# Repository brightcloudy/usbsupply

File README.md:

# USB Power Supply
USB-powered power supply board based around the LTC3883 Power System Manager. 

## Specifications
- 0.5-5.0 V Output Range
- 400 mA Output Current
- Programmable Current Limit
- Programmable Output Voltage

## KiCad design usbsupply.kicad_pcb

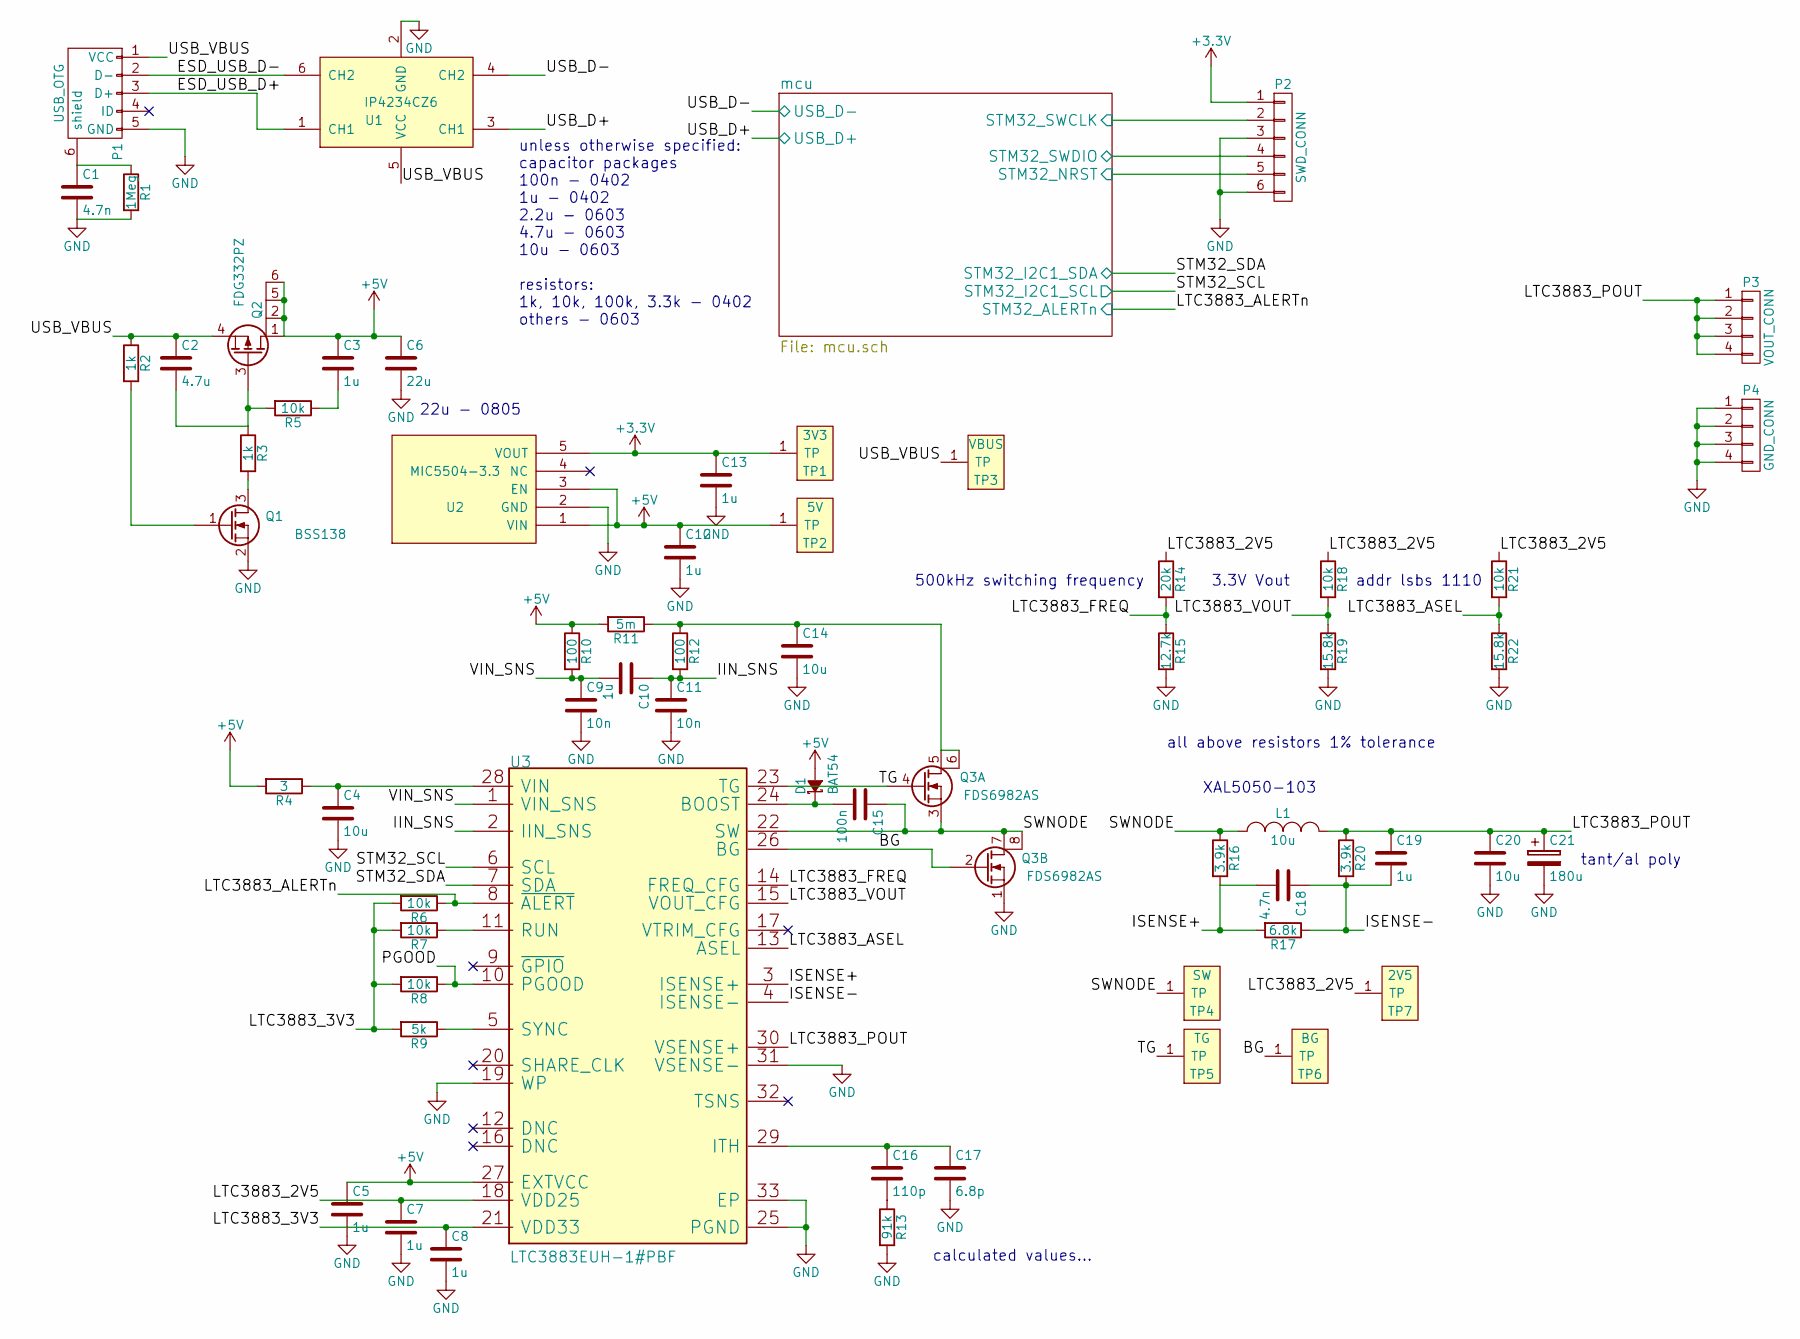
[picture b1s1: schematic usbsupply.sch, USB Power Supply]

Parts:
C1, C18: 4.7n; C_0603
C2: 4.7u; C_0603
C3, C5, C7, C8, C10, C12, C13, C19: 1u; C_0402
C4, C14, C20: 10u; C_0603
C6: 22u; C_0805
C9, C11: 10n; C_0402
C15: 100n; C_0402
C16: 110p; C_0603
C17: 6.8p; C_0603
C21: 180u; TantalC_SizeD_EIA-7343_Reflow
D1: BAT54; SOT-23
L1: 10u; XAL5050
P1: USB_OTG; USB_Mini-B
P2: SWD_CONN; Pin_Header_Straight_1x06
P3: VOUT_CONN; Pin_Header_Straight_1x04
P4: GND_CONN; Pin_Header_Straight_1x04
Q1: BSS138; SOT-23
Q2: FDG332PZ; SC-70-6
Q3: FDS6982AS; SOIC-8_3.9x4.9mm_Pitch1.27mm
R1: 1Meg; R_0805
R2, R3: 1k; R_0402
R4: 3; R_0805
R5, R6, R7, R8, R18, R21: 10k; R_0402
R9: 5k; R_0603
R10, R12: 100; R_0402
R11: 5m; R_1206
R13: 91k; R_0603
R14: 20k; R_0603
R15: 12.7k; R_0603
R16, R20: 3.9k; R_0603
R17: 6.8k; R_0603
R19, R22: 15.8k; R_0603
TP1: 3V3; TP
TP2: 5V; TP
TP3: VBUS; TP
TP4: SW; TP
TP5: TG; TP
TP6: BG; TP
TP7: 2V5; TP
U1: IP4234CZ6; SOT457
U2: MIC5504-3.3; SOT-23-5
U3: LTC3883EUH-1#PBF; QFN-32-1EP_5x5mm_Pitch0.5mm

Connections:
+3V3: C13.1, P2.1, TP1.1, U2.5 (VOUT); also elsewhere on the board
+5V: C3.1, C5.1, C6.1, C12.1, D1.2 (A), Q2.1 (D), Q2.2 (D), Q2.5 (D), Q2.6 (D), R4.2, R10.1, R11.2, TP2.1, U2.1 (VIN), U2.3 (EN), U3.27 (EXTVCC); also elsewhere on the board
/BG: Q3.2 (G), TP6.1, U3.26 (BG)
/ESD_USB_D+: P1.3 (D+), U1.1 (CH1)
/ESD_USB_D-: P1.2 (D-), U1.6 (CH2)
/IIN_SNS: C10.1, C11.1, R12.2, U3.2 (IIN_SNS)
/ISENSE+: C18.2, R16.2, R17.2, U3.3 (ISENSE+)
/ISENSE-: C18.1, C19.2, R17.1, R20.2, U3.4 (ISENSE-)
/LTC3883_2V5: C7.1, R14.1, R18.1, R21.1, TP7.1, U3.18 (VDD25)
/LTC3883_3V3: C8.1, R6.2, R7.2, R8.2, R9.2, U3.21 (VDD33)
/LTC3883_ASEL: R21.2, R22.1, U3.13 (ASEL)
/LTC3883_FREQ: R14.2, R15.1, U3.14 (FREQ_CFG)
/LTC3883_POUT: C19.1, C20.1, C21.1, L1.2, P3.1, P3.2, P3.3, P3.4, R20.1, U3.30 (VSENSE+)
/LTC3883_VOUT: R18.2, R19.1, U3.15 (VOUT_CFG)
/PGOOD: R8.1, U3.10 (PGOOD)
/SWNODE: C15.1, L1.1, Q3.3 (S), Q3.7 (D), Q3.8 (D), R16.1, TP4.1, U3.22 (SW)
/TG: Q3.4 (G), TP5.1, U3.23 (TG)
/USB_VBUS: C2.1, P1.1 (VCC), Q2.4 (S), R2.1, TP3.1, U1.5 (VCC)
/VIN_SNS: C9.1, C10.2, R10.2, U3.1 (VIN_SNS)
/mcu/STM32_ALERTn: R6.1, U3.8 (~ALERT); also elsewhere on the board
/mcu/STM32_I2C1_SCL: U3.6 (SCL); also elsewhere on the board
/mcu/STM32_I2C1_SDA: U3.7 (SDA); also elsewhere on the board
/mcu/STM32_NRST: P2.5; also elsewhere on the board
/mcu/STM32_SWCLK: P2.2; also elsewhere on the board
/mcu/STM32_SWDIO: P2.4; also elsewhere on the board
/mcu/USB_D+: U1.3 (CH1); also elsewhere on the board
/mcu/USB_D-: U1.4 (CH2); also elsewhere on the board
GND: C1.2, C4.2, C5.2, C6.2, C7.2, C8.2, C9.2, C11.2, C12.2, C13.2, C14.2, C17.2, C20.2, C21.2, P1.5 (GND), P2.3, P2.6, P4.1, P4.2, P4.3, P4.4, Q1.2 (S), Q3.1 (S), R1.2, R13.2, R15.2, R19.2, R22.2, U1.2 (GND), U2.2 (GND), U3.19 (WP), U3.25 (PGND), U3.31 (VSENSE-), U3.33 (EP); also elsewhere on the board
unnamed: C1.1, P1.6 (shield), R1.1
unnamed: C2.2, Q2.3 (G), R3.1, R5.2
unnamed: C3.2, R5.1
unnamed: C4.1, R4.1, U3.28 (VIN)
unnamed: C14.1, Q3.5 (D), Q3.6 (D), R11.1, R12.1
unnamed: C15.2, D1.1 (K), U3.24 (BOOST)
unnamed: C16.1, C17.1, U3.29 (ITH)
unnamed: C16.2, R13.1
unnamed: Q1.1 (G), R2.2
unnamed: Q1.3 (D), R3.2
unnamed: R7.1, U3.11 (RUN)
unnamed: R9.1, U3.5 (SYNC)

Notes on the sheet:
unless otherwise specified: capacitor packages 100n - 0402 1u - 0402 2.2u - 0603 4.7u - 0603 10u - 0603 resistors: 1k, 10k, 100k, 3.3k - 0402 others - 0603
22u - 0805
XAL5050-103
calculated values...
tant/al poly
all above resistors 1% tolerance
3.3V Vout
500kHz switching frequency
addr lsbs 1110

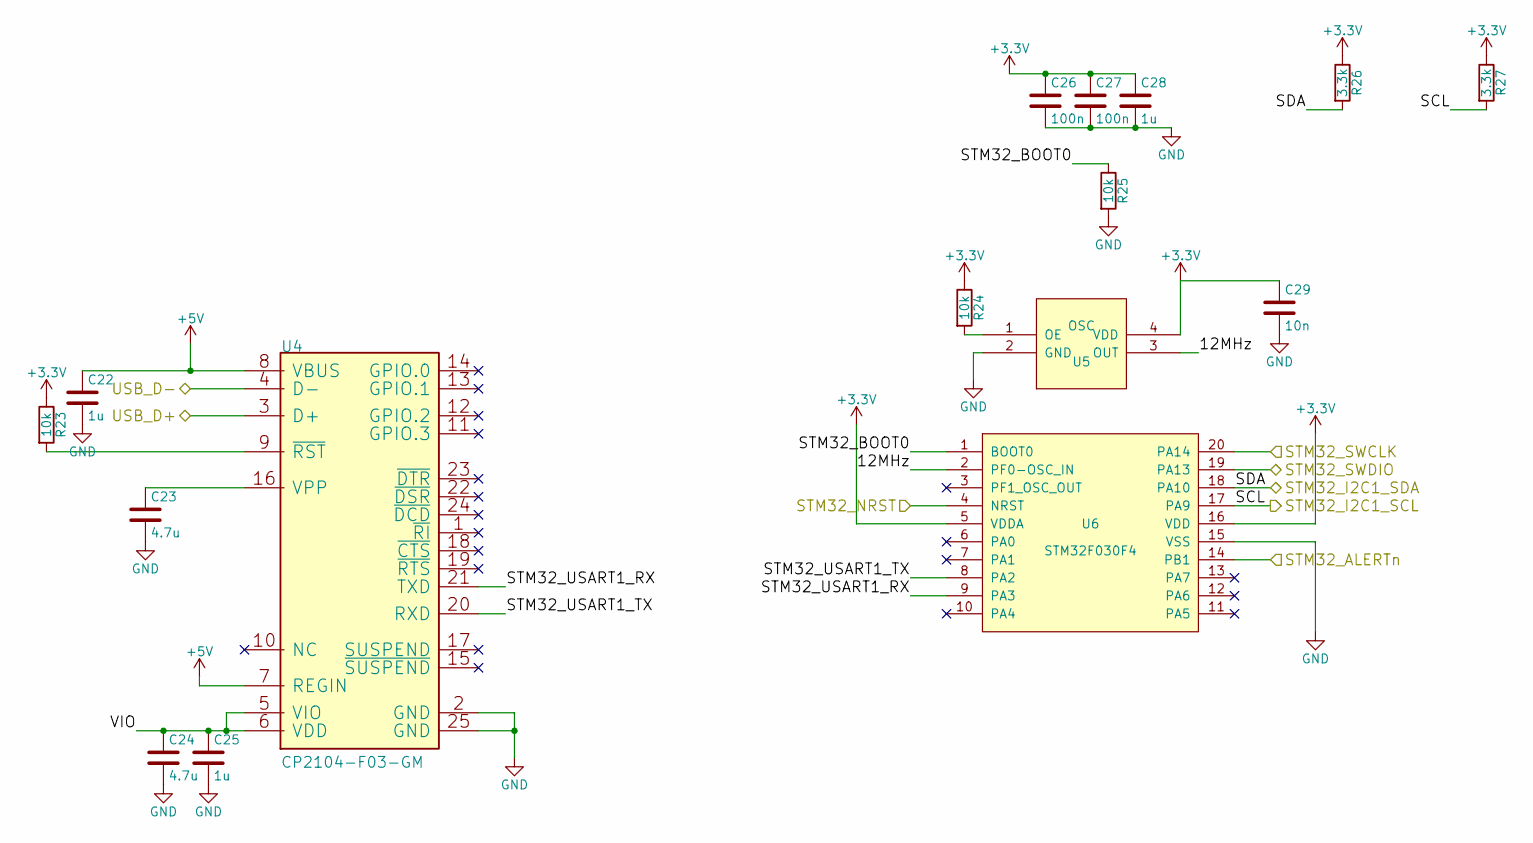
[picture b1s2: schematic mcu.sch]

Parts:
C22, C25, C28: 1u; C_0402
C23, C24: 4.7u; C_0603
C26, C27: 100n; C_0402
C29: 10n; C_0402
R23, R24, R25: 10k; R_0402
R26, R27: 3.3k; R_0402
U4: CP2104-F03-GM; QFN-24-1EP_4x4mm_Pitch0.5mm
U5: OSC; SIOSC
U6: STM32F030F4; TSSOP-20_4.4x6.5mm_Pitch0.65mm

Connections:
+3V3: C26.1, C27.1, C28.1, C29.1, R23.1, R24.1, R26.1, R27.1, U5.4 (VDD), U6.5 (VDDA), U6.16 (VDD); also elsewhere on the board
+5V: C22.1, U4.7 (REGIN), U4.8 (VBUS); also elsewhere on the board
/mcu/12MHz: U5.3 (OUT), U6.2 (PF0-OSC_IN)
/mcu/STM32_ALERTn: U6.14 (PB1); also elsewhere on the board
/mcu/STM32_BOOT0: R25.1, U6.1 (BOOT0)
/mcu/STM32_I2C1_SCL: R27.2, U6.17 (PA9); also elsewhere on the board
/mcu/STM32_I2C1_SDA: R26.2, U6.18 (PA10); also elsewhere on the board
/mcu/STM32_NRST: U6.4 (NRST); also elsewhere on the board
/mcu/STM32_SWCLK: U6.20 (PA14); also elsewhere on the board
/mcu/STM32_SWDIO: U6.19 (PA13); also elsewhere on the board
/mcu/STM32_USART1_RX: U4.21 (TXD), U6.9 (PA3)
/mcu/STM32_USART1_TX: U4.20 (RXD), U6.8 (PA2)
/mcu/USB_D+: U4.3 (D+); also elsewhere on the board
/mcu/USB_D-: U4.4 (D-); also elsewhere on the board
/mcu/VIO: C24.1, C25.1, U4.5 (VIO), U4.6 (VDD)
GND: C22.2, C23.2, C24.2, C25.2, C26.2, C27.2, C28.2, C29.2, R25.2, U4.2 (GND), U4.25 (GND), U5.2 (GND), U6.15 (VSS); also elsewhere on the board
unnamed: C23.1, U4.16 (VPP)
unnamed: R23.2, U4.9 (~RST)
unnamed: R24.2, U5.1 (OE)

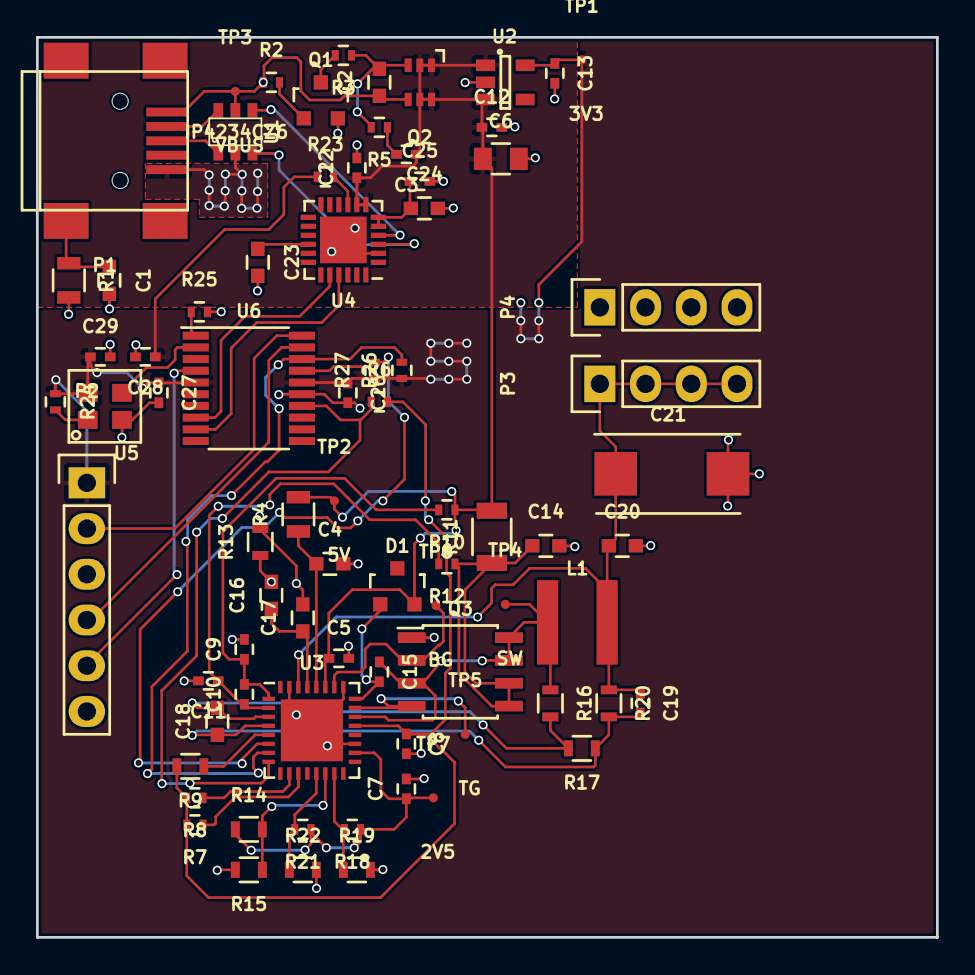
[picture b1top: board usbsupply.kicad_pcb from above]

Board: 2 copper layers, 50.0 x 50.0 mm, 78 parts (0 on the bottom side), 48 nets.

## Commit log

2016-01-19 Initial commit with partial schematic progress.
2016-01-19 Fix markdown in README
2016-01-19 Finish basic MCU + USB/UART bridge schematics.
2016-01-19 Completed most of the schematic work for the main LTC3883 IC.
2016-01-19 Add the config resistor dividers to the LTC3883 and output connectors, and a handful of test points. Schematic probably almost done at this point.
2016-01-25 Finish layout and routing of initial PCB revision.
2016-01-25 Update README.
